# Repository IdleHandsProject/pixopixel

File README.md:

# The PIXO Pixel
PIXO Pixel is a 16 x 16 RGB LED display that runs off of an ESP32.

This project is open source! 

If you want to build this yourself, you can find the Bill of Materials [here](https://www.findchips.com/org/10-open-hardware/list/85998-pixo-pixel-esp-board-and-led-board) on FindChips.

## Flashing Firmware Instructions
1. You need to have the current version of the [Arduino IDE](https://arduino.cc) installed
2. Ensure that you have the [Arduino ESP32 Boards](https://github.com/espressif/arduino-esp32) installed
3. Various other libraries are required for the example firmware; they are listed below under "Libraries used in Example Firmware"
4. Connect your pixo pixel to your computer and start Arduino
5. Under the "Tools" menu, select "Board->Adafruit ESP32 Feather"; Leave Flash frequency and Upload speed the default
6. Under Port, select the device your pixo is communicating over
7. Compile and upload
8. When the Arduino console says "Connecting....", press and hold both the boot and reset buttons simultaniously for 1 second; then release both buttons
9. You should start to see output about flashing
10. When the flash is complete, press the reset button on the pixo to start your new firmware

[Here](https://youtu.be/dVT4Nei8qHg) is a video of Sean going into detail demonstrating some of the examples

## Libraries used in Example Firmware
Install these to your sketchbook's `libraries` folder, usually located in `YOUR HOME/Documents/Arduino`

* [Adafruit GFX](https://github.com/adafruit/Adafruit-GFX-Library)
* [Adafruit DotStar](https://github.com/adafruit/Adafruit_DotStar)
* [Adafruit DotStar Matrix](https://github.com/adafruit/Adafruit_DotStarMatrix)
* [ArduinoJson](https://github.com/bblanchon/ArduinoJson)
* [i2cdevlib](https://github.com/jrowberg/i2cdevlib)

**Note** Arduino IDE was complaining about i2cdevlib being invalid as the installation instructions are a bit unclear.
It seems that the ESP32 is not officially supported for use with these libraries, and I had to apply a patch ([#367](https://github.com/jrowberg/i2cdevlib/pull/367)) to get no compile errors.

### Patching I2Cdev and MPU6050 Libraries
1. Download i2cdevlib and extract the zip file
2. Inside the i2cdevlib/Arduino folder, copy `I2Cdev` and `MPU6050` folders to your `libraries` folder
3. Edit `libraries/I2Cdev/I2Cdev.cpp`, and immedietly under `#include "I2Cdev.h"`, add the following
```
#ifdef ARDUINO_ARCH_ESP32
#define BUFFER_LENGTH I2C_BUFFER_LENGTH
#endif
```
4. Edit `libraries/MPU6050/MPU6050_6Axis_MotionApps20.h` and add the following right above the `DEBUG` section
```
#ifndef ARDUINO_ARCH_ESP32
    typedef void prog_void;
    typedef char prog_char;
    typedef unsigned char prog_uchar;
    typedef int8_t prog_int8_t;
    typedef uint8_t prog_uint8_t;
    typedef int16_t prog_int16_t;
    typedef uint16_t prog_uint16_t;
    typedef int32_t prog_int32_t;
    typedef uint32_t prog_uint32_t;
#endif
```
5. Restart Arduino

There's a whole bunch of other commits in here, but this seems mostly to be a mix of: feature adding, bug fixing, and various other changes that may or may not be related. Feel free to experiment with these at your own discretion.

## Kickstarter - Success
This was a [Make100 Kickstarter](https://www.kickstarter.com/projects/idlehandsdev/pixo-pixel-an-esp32-based-iot-rgb-display-for-make) that was recently fulfilled

[Completion Video](https://youtu.be/YA3uAYVbMNc)

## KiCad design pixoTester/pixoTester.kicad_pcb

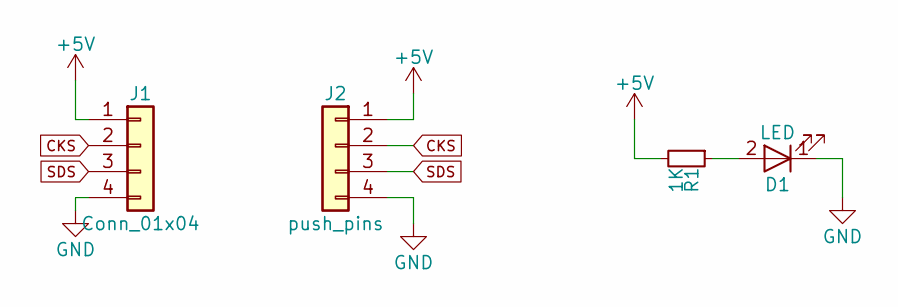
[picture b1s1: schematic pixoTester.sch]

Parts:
D1: LED; LED-0603
J1: Conn_01x04; Connectors_JST_S4B-PH-SM4-TB
J2: push_pins; pixo_testpins
R1: 1K; R_0805

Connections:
+5V: J1.1, J2.1, R1.2
CKS: J1.2, J2.2
GND: D1.1 (K), J1.4, J2.4
unnamed: D1.2 (A), R1.1
SDS: J1.3, J2.3

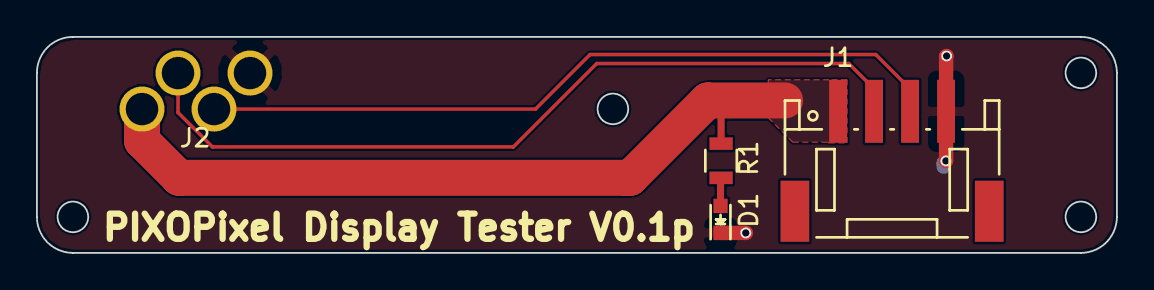
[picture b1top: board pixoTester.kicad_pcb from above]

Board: 2 copper layers, 60.0 x 12.0 mm, 4 parts (0 on the bottom side), 5 nets.

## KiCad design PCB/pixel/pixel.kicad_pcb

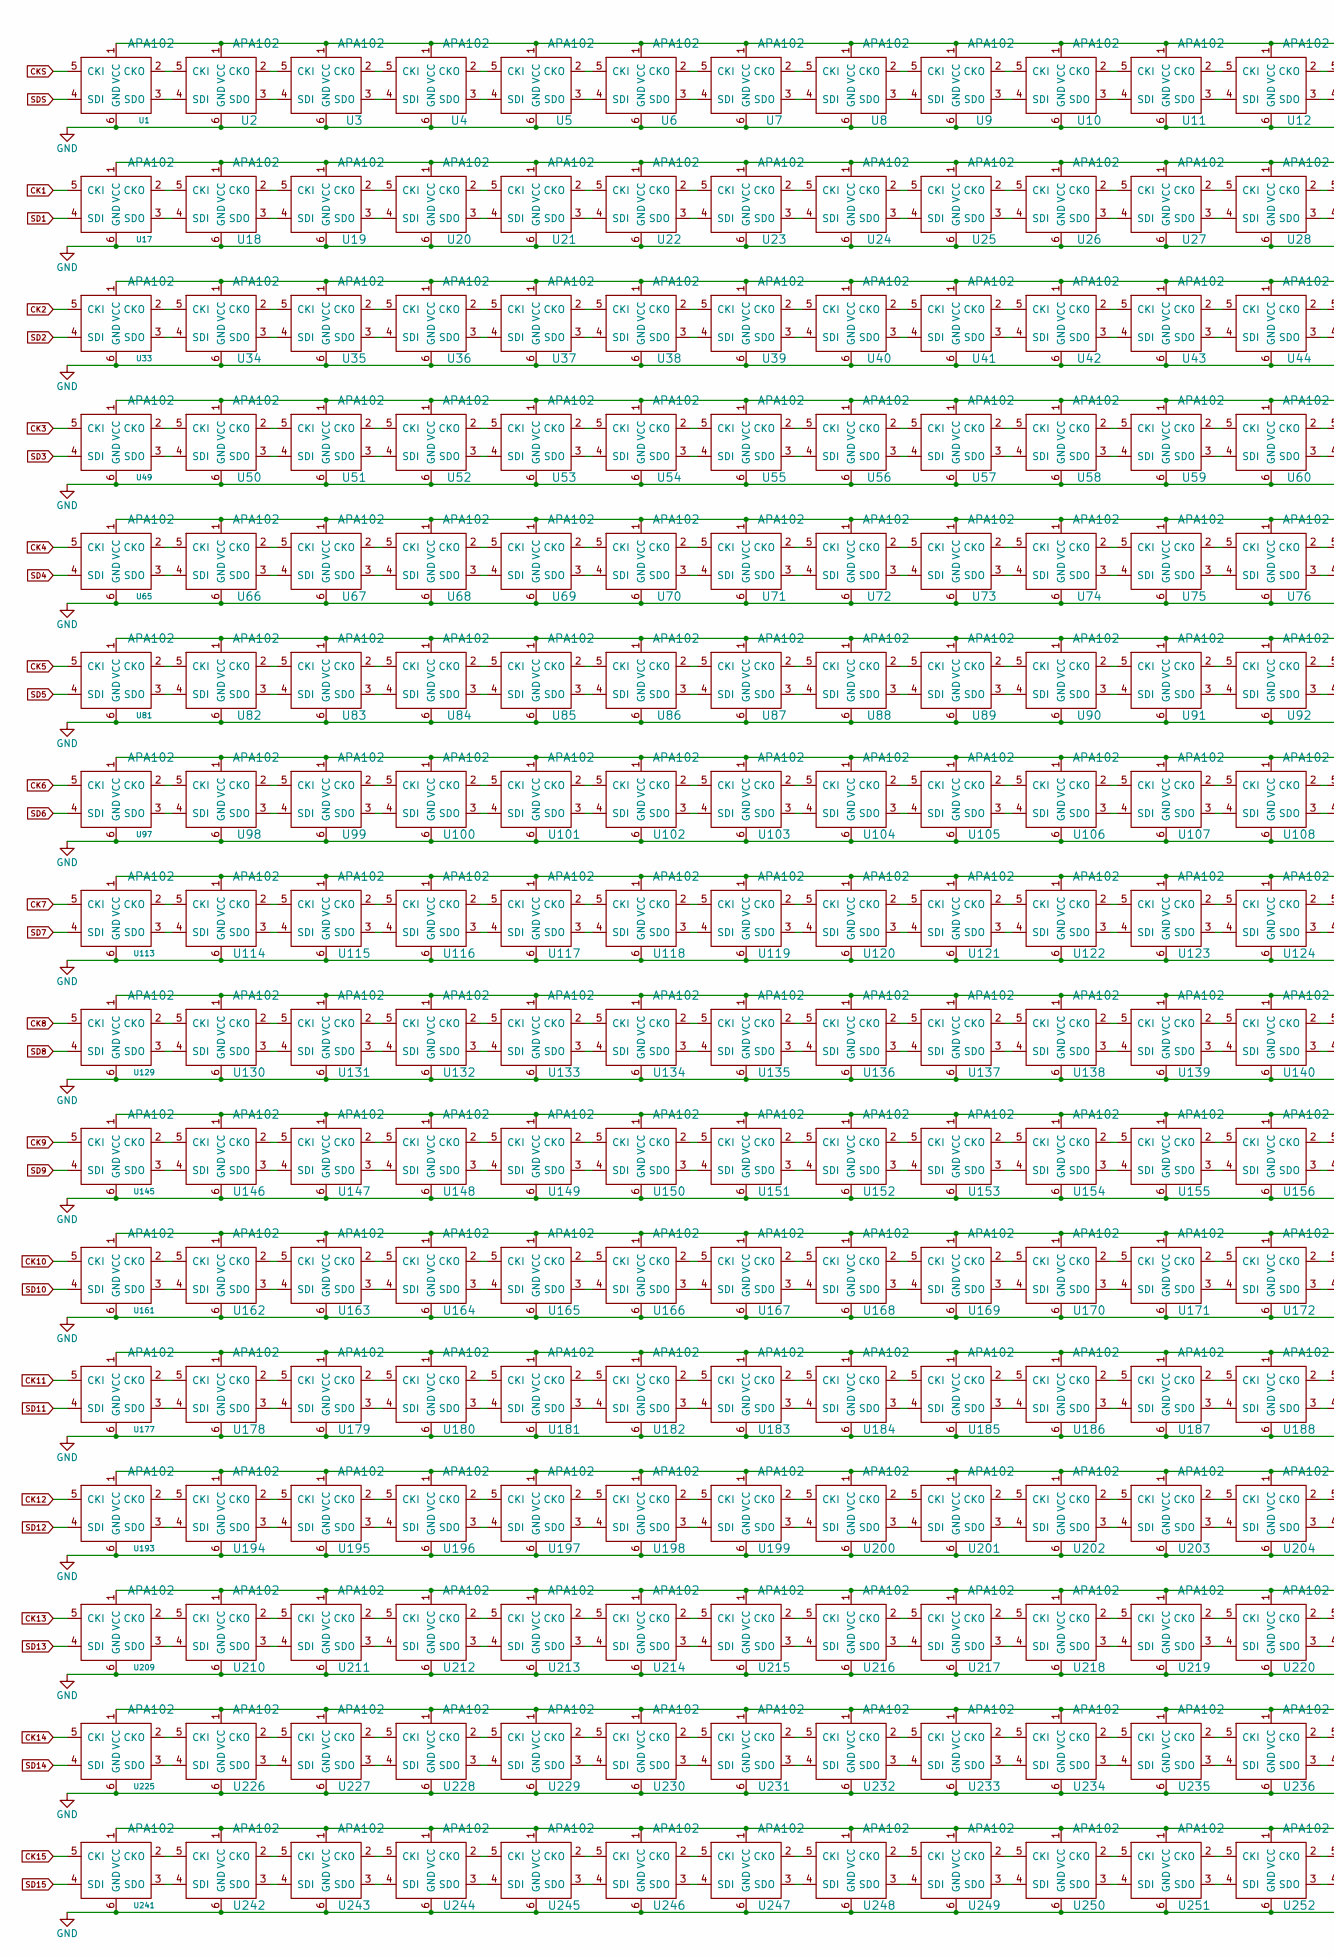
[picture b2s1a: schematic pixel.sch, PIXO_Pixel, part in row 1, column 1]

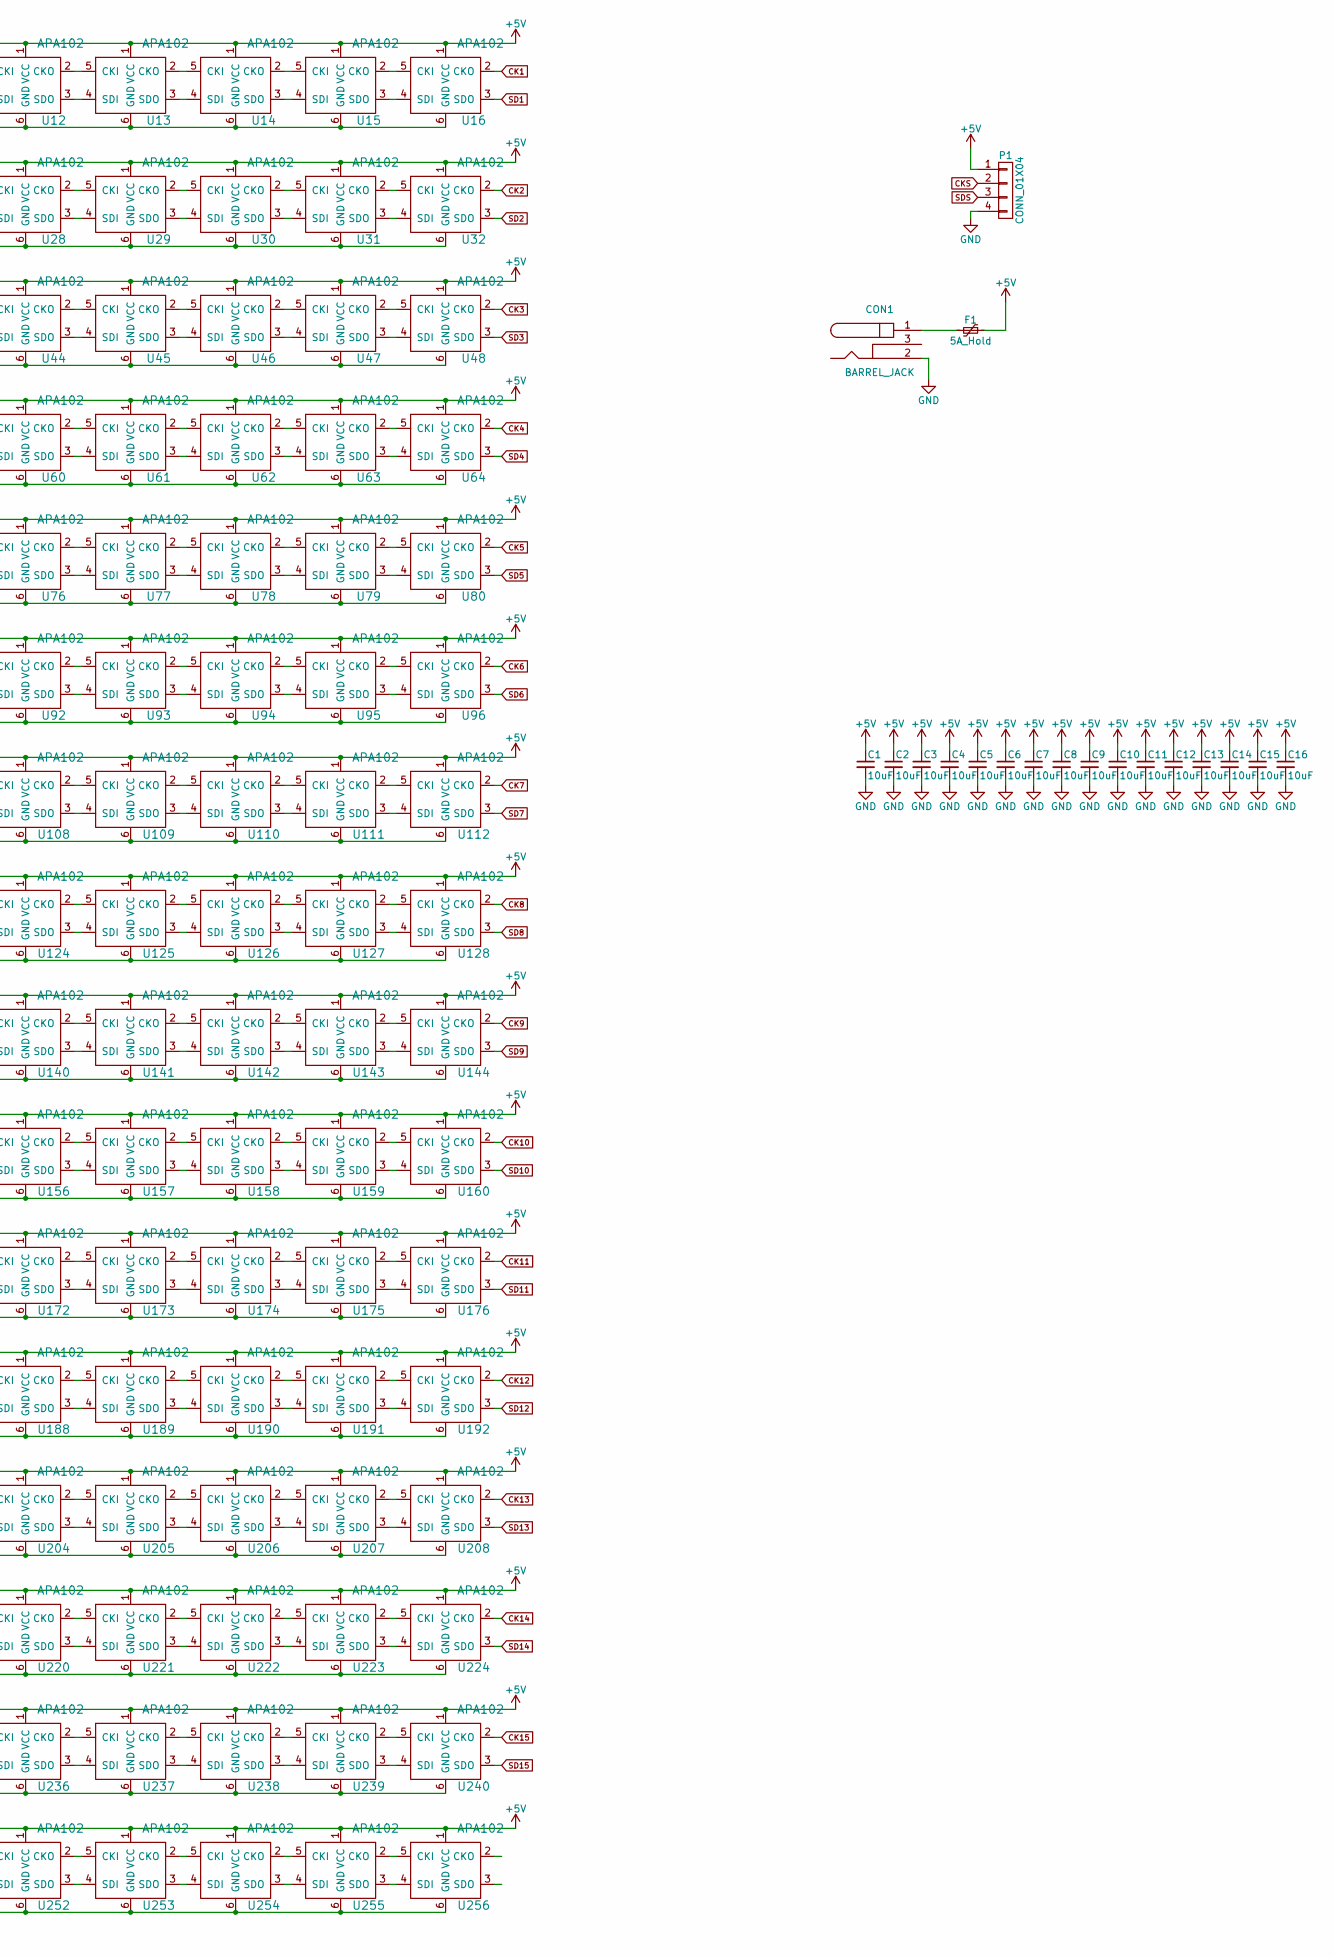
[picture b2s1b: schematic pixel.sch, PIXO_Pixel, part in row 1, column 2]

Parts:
C1: 10uF; c_1206; Digikey Part No. 490-3340-1-ND
C2, C3, C4, C5, C6, C7, C8, C9, C10, C11, C12, C13, C14, C15, C16: 10uF; c_1206; Digikey Part No. 490-5525-1-ND
CON1: BARREL_JACK; DC_POWERJACK_VERT_NoHoles; Digikey Part No. CP-006APJCT-ND
F1: 5A_Hold; Fuse_SMD1206_Reflow; Digikey Part No. MF-USML400-2CT-ND
P1: CONN_01X04; Connectors_JST_S4B-PH-SM4-TB; Digikey Part No. 455-1751-1-ND
U1, U2, U3, U4, U5, U6, U7, U8, U9, U10, U11, U12, U13, U14, U15, U16, U17, U18, U19, U20, U21, U22, U23, U24, U25, U26, U27, U28, U29, U30, U31, U32, U33, U34, U35, U36, U37, U38, U39, U40, U41, U42, U43, U44, U45, U46, U47, U48, U49, U50, U51, U52, U53, U54, U55, U56, U57, U58, U59, U60, U61, U62, U63, U64, U65, U66, U67, U68, U69, U70, U71, U72, U73, U74, U75, U76, U77, U78, U79, U80, U81, U82, U83, U84, U85, U86, U87, U88, U89, U90, U91, U92, U93, U94, U95, U96, U97, U98, U99, U100, U101, U102, U103, U104, U105, U106, U107, U108, U109, U110, U111, U112, U113, U114, U115, U116, U117, U118, U119, U120, U121, U122, U123, U124, U125, U126, U127, U128, U129, U130, U131, U132, U133, U134, U135, U136, U137, U138, U139, U140, U141, U142, U143, U144, U145, U146, U147, U148, U149, U150, U151, U152, U153, U154, U155, U156, U157, U158, U159, U160, U161, U162, U163, U164, U165, U166, U167, U168, U169, U170, U171, U172, U173, U174, U175, U176, U177, U178, U179, U180, U181, U182, U183, U184, U185, U186, U187, U188, U189, U190, U191, U192, U193, U194, U195, U196, U197, U198, U199, U200, U201, U202, U203, U204, U205, U206, U207, U208, U209, U210, U211, U212, U213, U214, U215, U216, U217, U218, U219, U220, U221, U222, U223, U224, U225, U226, U227, U228, U229, U230, U231, U232, U233, U234, U235, U236, U237, U238, U239, U240, U241, U242, U243, U244, U245, U246, U247, U248, U249, U250, U251, U252, U253, U254, U255, U256: APA102; APA102-2020_AFSTYLE

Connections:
+5V: C1.1, C2.1, C3.1, C4.1, C5.1, C6.1, C7.1, C8.1, C9.1, C10.1, C11.1, C12.1, C13.1, C14.1, C15.1, C16.1, F1.1, P1.1, U1.1 (VCC), U2.1 (VCC), U3.1 (VCC), U4.1 (VCC), U5.1 (VCC), U6.1 (VCC), U7.1 (VCC), U8.1 (VCC), U9.1 (VCC), U10.1 (VCC), U11.1 (VCC), U12.1 (VCC), U13.1 (VCC), U14.1 (VCC), U15.1 (VCC), U16.1 (VCC), U17.1 (VCC), U18.1 (VCC), U19.1 (VCC), U20.1 (VCC), U21.1 (VCC), U22.1 (VCC), U23.1 (VCC), U24.1 (VCC), U25.1 (VCC), U26.1 (VCC), U27.1 (VCC), U28.1 (VCC), U29.1 (VCC), U30.1 (VCC), U31.1 (VCC), U32.1 (VCC), U33.1 (VCC), U34.1 (VCC), U35.1 (VCC), U36.1 (VCC), U37.1 (VCC), U38.1 (VCC), U39.1 (VCC), U40.1 (VCC), U41.1 (VCC), U42.1 (VCC), U43.1 (VCC), U44.1 (VCC), U45.1 (VCC), U46.1 (VCC), U47.1 (VCC), U48.1 (VCC), U49.1 (VCC), U50.1 (VCC), U51.1 (VCC), U52.1 (VCC), U53.1 (VCC), U54.1 (VCC), U55.1 (VCC), U56.1 (VCC), U57.1 (VCC), U58.1 (VCC), U59.1 (VCC), U60.1 (VCC), U61.1 (VCC), U62.1 (VCC), U63.1 (VCC), U64.1 (VCC), U65.1 (VCC), U66.1 (VCC), U67.1 (VCC), U68.1 (VCC), U69.1 (VCC), U70.1 (VCC), U71.1 (VCC), U72.1 (VCC), U73.1 (VCC), U74.1 (VCC), U75.1 (VCC), U76.1 (VCC), U77.1 (VCC), U78.1 (VCC), U79.1 (VCC), U80.1 (VCC), U81.1 (VCC), U82.1 (VCC), U83.1 (VCC), U84.1 (VCC), U85.1 (VCC), U86.1 (VCC), U87.1 (VCC), U88.1 (VCC), U89.1 (VCC), U90.1 (VCC), U91.1 (VCC), U92.1 (VCC), U93.1 (VCC), U94.1 (VCC), U95.1 (VCC), U96.1 (VCC), U97.1 (VCC), U98.1 (VCC), U99.1 (VCC), U100.1 (VCC), U101.1 (VCC), U102.1 (VCC), U103.1 (VCC), U104.1 (VCC), U105.1 (VCC), U106.1 (VCC), U107.1 (VCC), U108.1 (VCC), U109.1 (VCC), U110.1 (VCC), U111.1 (VCC), U112.1 (VCC), U113.1 (VCC), U114.1 (VCC), U115.1 (VCC), U116.1 (VCC), U117.1 (VCC), U118.1 (VCC), U119.1 (VCC), U120.1 (VCC), U121.1 (VCC), U122.1 (VCC), U123.1 (VCC), U124.1 (VCC), U125.1 (VCC), U126.1 (VCC), U127.1 (VCC), U128.1 (VCC), U129.1 (VCC), U130.1 (VCC), U131.1 (VCC), U132.1 (VCC), U133.1 (VCC), U134.1 (VCC), U135.1 (VCC), U136.1 (VCC), U137.1 (VCC), U138.1 (VCC), U139.1 (VCC), U140.1 (VCC), U141.1 (VCC), U142.1 (VCC), U143.1 (VCC), U144.1 (VCC), U145.1 (VCC), U146.1 (VCC), U147.1 (VCC), U148.1 (VCC), U149.1 (VCC), U150.1 (VCC), U151.1 (VCC), U152.1 (VCC), U153.1 (VCC), U154.1 (VCC), U155.1 (VCC), U156.1 (VCC), U157.1 (VCC), U158.1 (VCC), U159.1 (VCC), U160.1 (VCC), U161.1 (VCC), U162.1 (VCC), U163.1 (VCC), U164.1 (VCC), U165.1 (VCC), U166.1 (VCC), U167.1 (VCC), U168.1 (VCC), U169.1 (VCC), U170.1 (VCC), U171.1 (VCC), U172.1 (VCC), U173.1 (VCC), U174.1 (VCC), U175.1 (VCC), U176.1 (VCC), U177.1 (VCC), U178.1 (VCC), U179.1 (VCC), U180.1 (VCC), U181.1 (VCC), U182.1 (VCC), U183.1 (VCC), U184.1 (VCC), U185.1 (VCC), U186.1 (VCC), U187.1 (VCC), U188.1 (VCC), U189.1 (VCC), U190.1 (VCC), U191.1 (VCC), U192.1 (VCC), U193.1 (VCC), U194.1 (VCC), U195.1 (VCC), U196.1 (VCC), U197.1 (VCC), U198.1 (VCC), U199.1 (VCC), U200.1 (VCC), U201.1 (VCC), U202.1 (VCC), U203.1 (VCC), U204.1 (VCC), U205.1 (VCC), U206.1 (VCC), U207.1 (VCC), U208.1 (VCC), U209.1 (VCC), U210.1 (VCC), U211.1 (VCC), U212.1 (VCC), U213.1 (VCC), U214.1 (VCC), U215.1 (VCC), U216.1 (VCC), U217.1 (VCC), U218.1 (VCC), U219.1 (VCC), U220.1 (VCC), U221.1 (VCC), U222.1 (VCC), U223.1 (VCC), U224.1 (VCC), U225.1 (VCC), U226.1 (VCC), U227.1 (VCC), U228.1 (VCC), U229.1 (VCC), U230.1 (VCC), U231.1 (VCC), U232.1 (VCC), U233.1 (VCC), U234.1 (VCC), U235.1 (VCC), U236.1 (VCC), U237.1 (VCC), U238.1 (VCC), U239.1 (VCC), U240.1 (VCC), U241.1 (VCC), U242.1 (VCC), U243.1 (VCC), U244.1 (VCC), U245.1 (VCC), U246.1 (VCC), U247.1 (VCC), U248.1 (VCC), U249.1 (VCC), U250.1 (VCC), U251.1 (VCC), U252.1 (VCC), U253.1 (VCC), U254.1 (VCC), U255.1 (VCC), U256.1 (VCC)
CK1: U16.2 (CKO), U17.5 (CKI)
CK2: U32.2 (CKO), U33.5 (CKI)
CK3: U48.2 (CKO), U49.5 (CKI)
CK4: U64.2 (CKO), U65.5 (CKI)
CK5: U80.2 (CKO), U81.5 (CKI)
CK6: U96.2 (CKO), U97.5 (CKI)
CK7: U112.2 (CKO), U113.5 (CKI)
CK8: U128.2 (CKO), U129.5 (CKI)
CK9: U144.2 (CKO), U145.5 (CKI)
CK10: U160.2 (CKO), U161.5 (CKI)
CK11: U176.2 (CKO), U177.5 (CKI)
CK12: U192.2 (CKO), U193.5 (CKI)
CK13: U208.2 (CKO), U209.5 (CKI)
CK14: U224.2 (CKO), U225.5 (CKI)
CK15: U240.2 (CKO), U241.5 (CKI)
CKS: P1.2, U1.5 (CKI)
GND: C1.2, C2.2, C3.2, C4.2, C5.2, C6.2, C7.2, C8.2, C9.2, C10.2, C11.2, C12.2, C13.2, C14.2, C15.2, C16.2, CON1.2, P1.4, U1.6 (GND), U2.6 (GND), U3.6 (GND), U4.6 (GND), U5.6 (GND), U6.6 (GND), U7.6 (GND), U8.6 (GND), U9.6 (GND), U10.6 (GND), U11.6 (GND), U12.6 (GND), U13.6 (GND), U14.6 (GND), U15.6 (GND), U16.6 (GND), U17.6 (GND), U18.6 (GND), U19.6 (GND), U20.6 (GND), U21.6 (GND), U22.6 (GND), U23.6 (GND), U24.6 (GND), U25.6 (GND), U26.6 (GND), U27.6 (GND), U28.6 (GND), U29.6 (GND), U30.6 (GND), U31.6 (GND), U32.6 (GND), U33.6 (GND), U34.6 (GND), U35.6 (GND), U36.6 (GND), U37.6 (GND), U38.6 (GND), U39.6 (GND), U40.6 (GND), U41.6 (GND), U42.6 (GND), U43.6 (GND), U44.6 (GND), U45.6 (GND), U46.6 (GND), U47.6 (GND), U48.6 (GND), U49.6 (GND), U50.6 (GND), U51.6 (GND), U52.6 (GND), U53.6 (GND), U54.6 (GND), U55.6 (GND), U56.6 (GND), U57.6 (GND), U58.6 (GND), U59.6 (GND), U60.6 (GND), U61.6 (GND), U62.6 (GND), U63.6 (GND), U64.6 (GND), U65.6 (GND), U66.6 (GND), U67.6 (GND), U68.6 (GND), U69.6 (GND), U70.6 (GND), U71.6 (GND), U72.6 (GND), U73.6 (GND), U74.6 (GND), U75.6 (GND), U76.6 (GND), U77.6 (GND), U78.6 (GND), U79.6 (GND), U80.6 (GND), U81.6 (GND), U82.6 (GND), U83.6 (GND), U84.6 (GND), U85.6 (GND), U86.6 (GND), U87.6 (GND), U88.6 (GND), U89.6 (GND), U90.6 (GND), U91.6 (GND), U92.6 (GND), U93.6 (GND), U94.6 (GND), U95.6 (GND), U96.6 (GND), U97.6 (GND), U98.6 (GND), U99.6 (GND), U100.6 (GND), U101.6 (GND), U102.6 (GND), U103.6 (GND), U104.6 (GND), U105.6 (GND), U106.6 (GND), U107.6 (GND), U108.6 (GND), U109.6 (GND), U110.6 (GND), U111.6 (GND), U112.6 (GND), U113.6 (GND), U114.6 (GND), U115.6 (GND), U116.6 (GND), U117.6 (GND), U118.6 (GND), U119.6 (GND), U120.6 (GND), U121.6 (GND), U122.6 (GND), U123.6 (GND), U124.6 (GND), U125.6 (GND), U126.6 (GND), U127.6 (GND), U128.6 (GND), U129.6 (GND), U130.6 (GND), U131.6 (GND), U132.6 (GND), U133.6 (GND), U134.6 (GND), U135.6 (GND), U136.6 (GND), U137.6 (GND), U138.6 (GND), U139.6 (GND), U140.6 (GND), U141.6 (GND), U142.6 (GND), U143.6 (GND), U144.6 (GND), U145.6 (GND), U146.6 (GND), U147.6 (GND), U148.6 (GND), U149.6 (GND), U150.6 (GND), U151.6 (GND), U152.6 (GND), U153.6 (GND), U154.6 (GND), U155.6 (GND), U156.6 (GND), U157.6 (GND), U158.6 (GND), U159.6 (GND), U160.6 (GND), U161.6 (GND), U162.6 (GND), U163.6 (GND), U164.6 (GND), U165.6 (GND), U166.6 (GND), U167.6 (GND), U168.6 (GND), U169.6 (GND), U170.6 (GND), U171.6 (GND), U172.6 (GND), U173.6 (GND), U174.6 (GND), U175.6 (GND), U176.6 (GND), U177.6 (GND), U178.6 (GND), U179.6 (GND), U180.6 (GND), U181.6 (GND), U182.6 (GND), U183.6 (GND), U184.6 (GND), U185.6 (GND), U186.6 (GND), U187.6 (GND), U188.6 (GND), U189.6 (GND), U190.6 (GND), U191.6 (GND), U192.6 (GND), U193.6 (GND), U194.6 (GND), U195.6 (GND), U196.6 (GND), U197.6 (GND), U198.6 (GND), U199.6 (GND), U200.6 (GND), U201.6 (GND), U202.6 (GND), U203.6 (GND), U204.6 (GND), U205.6 (GND), U206.6 (GND), U207.6 (GND), U208.6 (GND), U209.6 (GND), U210.6 (GND), U211.6 (GND), U212.6 (GND), U213.6 (GND), U214.6 (GND), U215.6 (GND), U216.6 (GND), U217.6 (GND), U218.6 (GND), U219.6 (GND), U220.6 (GND), U221.6 (GND), U222.6 (GND), U223.6 (GND), U224.6 (GND), U225.6 (GND), U226.6 (GND), U227.6 (GND), U228.6 (GND), U229.6 (GND), U230.6 (GND), U231.6 (GND), U232.6 (GND), U233.6 (GND), U234.6 (GND), U235.6 (GND), U236.6 (GND), U237.6 (GND), U238.6 (GND), U239.6 (GND), U240.6 (GND), U241.6 (GND), U242.6 (GND), U243.6 (GND), U244.6 (GND), U245.6 (GND), U246.6 (GND), U247.6 (GND), U248.6 (GND), U249.6 (GND), U250.6 (GND), U251.6 (GND), U252.6 (GND), U253.6 (GND), U254.6 (GND), U255.6 (GND), U256.6 (GND)
unnamed: CON1.1, F1.2
unnamed: U1.2 (CKO), U2.5 (CKI)
unnamed: U1.3 (SDO), U2.4 (SDI)
unnamed: U2.2 (CKO), U3.5 (CKI)
unnamed: U2.3 (SDO), U3.4 (SDI)
unnamed: U3.2 (CKO), U4.5 (CKI)
unnamed: U3.3 (SDO), U4.4 (SDI)
unnamed: U4.2 (CKO), U5.5 (CKI)
unnamed: U4.3 (SDO), U5.4 (SDI)
unnamed: U5.2 (CKO), U6.5 (CKI)
unnamed: U5.3 (SDO), U6.4 (SDI)
unnamed: U6.2 (CKO), U7.5 (CKI)
unnamed: U6.3 (SDO), U7.4 (SDI)
unnamed: U7.2 (CKO), U8.5 (CKI)
unnamed: U7.3 (SDO), U8.4 (SDI)
unnamed: U8.2 (CKO), U9.5 (CKI)
unnamed: U8.3 (SDO), U9.4 (SDI)
unnamed: U10.2 (CKO), U11.5 (CKI)
unnamed: U10.3 (SDO), U11.4 (SDI)
unnamed: U9.3 (SDO), U10.4 (SDI)
unnamed: U9.2 (CKO), U10.5 (CKI)
unnamed: U11.2 (CKO), U12.5 (CKI)
unnamed: U11.3 (SDO), U12.4 (SDI)
unnamed: U12.2 (CKO), U13.5 (CKI)
unnamed: U12.3 (SDO), U13.4 (SDI)
unnamed: U13.2 (CKO), U14.5 (CKI)
unnamed: U13.3 (SDO), U14.4 (SDI)
unnamed: U14.2 (CKO), U15.5 (CKI)
unnamed: U14.3 (SDO), U15.4 (SDI)
unnamed: U15.2 (CKO), U16.5 (CKI)
unnamed: U15.3 (SDO), U16.4 (SDI)
unnamed: U17.2 (CKO), U18.5 (CKI)
unnamed: U17.3 (SDO), U18.4 (SDI)
unnamed: U18.2 (CKO), U19.5 (CKI)
unnamed: U18.3 (SDO), U19.4 (SDI)
unnamed: U19.2 (CKO), U20.5 (CKI)
unnamed: U19.3 (SDO), U20.4 (SDI)
unnamed: U20.2 (CKO), U21.5 (CKI)
unnamed: U20.3 (SDO), U21.4 (SDI)
unnamed: U21.2 (CKO), U22.5 (CKI)
unnamed: U21.3 (SDO), U22.4 (SDI)
unnamed: U22.2 (CKO), U23.5 (CKI)
unnamed: U22.3 (SDO), U23.4 (SDI)
unnamed: U23.2 (CKO), U24.5 (CKI)
unnamed: U23.3 (SDO), U24.4 (SDI)
unnamed: U24.2 (CKO), U25.5 (CKI)
unnamed: U24.3 (SDO), U25.4 (SDI)
unnamed: U25.2 (CKO), U26.5 (CKI)
unnamed: U25.3 (SDO), U26.4 (SDI)
unnamed: U26.2 (CKO), U27.5 (CKI)
unnamed: U26.3 (SDO), U27.4 (SDI)
unnamed: U27.2 (CKO), U28.5 (CKI)
unnamed: U27.3 (SDO), U28.4 (SDI)
unnamed: U28.2 (CKO), U29.5 (CKI)
unnamed: U28.3 (SDO), U29.4 (SDI)
unnamed: U29.2 (CKO), U30.5 (CKI)
unnamed: U29.3 (SDO), U30.4 (SDI)
unnamed: U30.2 (CKO), U31.5 (CKI)
unnamed: U30.3 (SDO), U31.4 (SDI)
unnamed: U31.2 (CKO), U32.5 (CKI)
unnamed: U31.3 (SDO), U32.4 (SDI)
unnamed: U33.2 (CKO), U34.5 (CKI)
unnamed: U33.3 (SDO), U34.4 (SDI)
unnamed: U34.2 (CKO), U35.5 (CKI)
unnamed: U34.3 (SDO), U35.4 (SDI)
unnamed: U35.2 (CKO), U36.5 (CKI)
unnamed: U35.3 (SDO), U36.4 (SDI)
unnamed: U36.2 (CKO), U37.5 (CKI)
unnamed: U36.3 (SDO), U37.4 (SDI)
unnamed: U37.2 (CKO), U38.5 (CKI)
unnamed: U37.3 (SDO), U38.4 (SDI)
unnamed: U38.2 (CKO), U39.5 (CKI)
unnamed: U38.3 (SDO), U39.4 (SDI)
unnamed: U39.2 (CKO), U40.5 (CKI)
unnamed: U39.3 (SDO), U40.4 (SDI)
unnamed: U40.2 (CKO), U41.5 (CKI)
unnamed: U40.3 (SDO), U41.4 (SDI)
unnamed: U41.2 (CKO), U42.5 (CKI)
unnamed: U41.3 (SDO), U42.4 (SDI)
unnamed: U42.2 (CKO), U43.5 (CKI)
unnamed: U42.3 (SDO), U43.4 (SDI)
unnamed: U43.2 (CKO), U44.5 (CKI)
unnamed: U43.3 (SDO), U44.4 (SDI)
unnamed: U44.2 (CKO), U45.5 (CKI)
unnamed: U44.3 (SDO), U45.4 (SDI)
unnamed: U45.2 (CKO), U46.5 (CKI)
unnamed: U45.3 (SDO), U46.4 (SDI)
unnamed: U46.2 (CKO), U47.5 (CKI)
unnamed: U46.3 (SDO), U47.4 (SDI)
unnamed: U47.2 (CKO), U48.5 (CKI)
unnamed: U47.3 (SDO), U48.4 (SDI)
unnamed: U49.2 (CKO), U50.5 (CKI)
unnamed: U49.3 (SDO), U50.4 (SDI)
unnamed: U50.2 (CKO), U51.5 (CKI)
unnamed: U50.3 (SDO), U51.4 (SDI)
unnamed: U51.2 (CKO), U52.5 (CKI)
unnamed: U51.3 (SDO), U52.4 (SDI)
unnamed: U52.2 (CKO), U53.5 (CKI)
unnamed: U52.3 (SDO), U53.4 (SDI)
unnamed: U53.2 (CKO), U54.5 (CKI)
unnamed: U53.3 (SDO), U54.4 (SDI)
unnamed: U54.2 (CKO), U55.5 (CKI)
unnamed: U54.3 (SDO), U55.4 (SDI)
unnamed: U55.2 (CKO), U56.5 (CKI)
unnamed: U55.3 (SDO), U56.4 (SDI)
unnamed: U56.2 (CKO), U57.5 (CKI)
unnamed: U56.3 (SDO), U57.4 (SDI)
unnamed: U57.2 (CKO), U58.5 (CKI)
unnamed: U57.3 (SDO), U58.4 (SDI)
unnamed: U58.2 (CKO), U59.5 (CKI)
unnamed: U58.3 (SDO), U59.4 (SDI)
unnamed: U59.2 (CKO), U60.5 (CKI)
unnamed: U59.3 (SDO), U60.4 (SDI)
unnamed: U60.2 (CKO), U61.5 (CKI)
unnamed: U60.3 (SDO), U61.4 (SDI)
unnamed: U61.2 (CKO), U62.5 (CKI)
unnamed: U61.3 (SDO), U62.4 (SDI)
unnamed: U62.2 (CKO), U63.5 (CKI)
unnamed: U62.3 (SDO), U63.4 (SDI)
unnamed: U63.2 (CKO), U64.5 (CKI)
unnamed: U63.3 (SDO), U64.4 (SDI)
unnamed: U65.2 (CKO), U66.5 (CKI)
unnamed: U65.3 (SDO), U66.4 (SDI)
unnamed: U66.2 (CKO), U67.5 (CKI)
unnamed: U66.3 (SDO), U67.4 (SDI)
unnamed: U67.2 (CKO), U68.5 (CKI)
unnamed: U67.3 (SDO), U68.4 (SDI)
unnamed: U68.2 (CKO), U69.5 (CKI)
unnamed: U68.3 (SDO), U69.4 (SDI)
unnamed: U69.2 (CKO), U70.5 (CKI)
unnamed: U69.3 (SDO), U70.4 (SDI)
unnamed: U70.2 (CKO), U71.5 (CKI)
unnamed: U70.3 (SDO), U71.4 (SDI)
unnamed: U71.2 (CKO), U72.5 (CKI)
unnamed: U71.3 (SDO), U72.4 (SDI)
unnamed: U72.2 (CKO), U73.5 (CKI)
unnamed: U72.3 (SDO), U73.4 (SDI)
unnamed: U73.2 (CKO), U74.5 (CKI)
unnamed: U73.3 (SDO), U74.4 (SDI)
unnamed: U74.2 (CKO), U75.5 (CKI)
unnamed: U74.3 (SDO), U75.4 (SDI)
unnamed: U75.2 (CKO), U76.5 (CKI)
unnamed: U75.3 (SDO), U76.4 (SDI)
unnamed: U76.2 (CKO), U77.5 (CKI)
unnamed: U76.3 (SDO), U77.4 (SDI)
unnamed: U77.2 (CKO), U78.5 (CKI)
unnamed: U77.3 (SDO), U78.4 (SDI)
unnamed: U78.2 (CKO), U79.5 (CKI)
unnamed: U78.3 (SDO), U79.4 (SDI)
unnamed: U79.2 (CKO), U80.5 (CKI)
unnamed: U79.3 (SDO), U80.4 (SDI)
unnamed: U81.2 (CKO), U82.5 (CKI)
unnamed: U81.3 (SDO), U82.4 (SDI)
unnamed: U82.2 (CKO), U83.5 (CKI)
unnamed: U82.3 (SDO), U83.4 (SDI)
unnamed: U83.2 (CKO), U84.5 (CKI)
unnamed: U83.3 (SDO), U84.4 (SDI)
unnamed: U84.2 (CKO), U85.5 (CKI)
unnamed: U84.3 (SDO), U85.4 (SDI)
unnamed: U85.2 (CKO), U86.5 (CKI)
unnamed: U85.3 (SDO), U86.4 (SDI)
unnamed: U86.2 (CKO), U87.5 (CKI)
unnamed: U86.3 (SDO), U87.4 (SDI)
unnamed: U87.2 (CKO), U88.5 (CKI)
unnamed: U87.3 (SDO), U88.4 (SDI)
unnamed: U88.2 (CKO), U89.5 (CKI)
unnamed: U88.3 (SDO), U89.4 (SDI)
unnamed: U89.2 (CKO), U90.5 (CKI)
unnamed: U89.3 (SDO), U90.4 (SDI)
unnamed: U90.2 (CKO), U91.5 (CKI)
unnamed: U90.3 (SDO), U91.4 (SDI)
unnamed: U91.2 (CKO), U92.5 (CKI)
unnamed: U91.3 (SDO), U92.4 (SDI)
unnamed: U92.2 (CKO), U93.5 (CKI)
unnamed: U92.3 (SDO), U93.4 (SDI)
unnamed: U93.2 (CKO), U94.5 (CKI)
unnamed: U93.3 (SDO), U94.4 (SDI)
unnamed: U94.2 (CKO), U95.5 (CKI)
unnamed: U94.3 (SDO), U95.4 (SDI)
unnamed: U95.2 (CKO), U96.5 (CKI)
unnamed: U95.3 (SDO), U96.4 (SDI)
unnamed: U97.2 (CKO), U98.5 (CKI)
unnamed: U97.3 (SDO), U98.4 (SDI)
unnamed: U98.2 (CKO), U99.5 (CKI)
unnamed: U98.3 (SDO), U99.4 (SDI)
unnamed: U100.2 (CKO), U101.5 (CKI)
unnamed: U100.3 (SDO), U101.4 (SDI)
unnamed: U99.3 (SDO), U100.4 (SDI)
unnamed: U99.2 (CKO), U100.5 (CKI)
unnamed: U101.2 (CKO), U102.5 (CKI)
unnamed: U101.3 (SDO), U102.4 (SDI)
unnamed: U102.2 (CKO), U103.5 (CKI)
unnamed: U102.3 (SDO), U103.4 (SDI)
unnamed: U103.2 (CKO), U104.5 (CKI)
unnamed: U103.3 (SDO), U104.4 (SDI)
unnamed: U104.2 (CKO), U105.5 (CKI)
unnamed: U104.3 (SDO), U105.4 (SDI)
unnamed: U105.2 (CKO), U106.5 (CKI)
unnamed: U105.3 (SDO), U106.4 (SDI)
unnamed: U106.2 (CKO), U107.5 (CKI)
unnamed: U106.3 (SDO), U107.4 (SDI)
unnamed: U107.2 (CKO), U108.5 (CKI)
unnamed: U107.3 (SDO), U108.4 (SDI)
unnamed: U108.2 (CKO), U109.5 (CKI)
unnamed: U108.3 (SDO), U109.4 (SDI)
unnamed: U109.2 (CKO), U110.5 (CKI)
unnamed: U109.3 (SDO), U110.4 (SDI)
unnamed: U110.2 (CKO), U111.5 (CKI)
unnamed: U110.3 (SDO), U111.4 (SDI)
unnamed: U111.2 (CKO), U112.5 (CKI)
unnamed: U111.3 (SDO), U112.4 (SDI)
unnamed: U113.2 (CKO), U114.5 (CKI)
unnamed: U113.3 (SDO), U114.4 (SDI)
unnamed: U114.2 (CKO), U115.5 (CKI)
unnamed: U114.3 (SDO), U115.4 (SDI)
unnamed: U115.2 (CKO), U116.5 (CKI)
unnamed: U115.3 (SDO), U116.4 (SDI)
unnamed: U116.2 (CKO), U117.5 (CKI)
unnamed: U116.3 (SDO), U117.4 (SDI)
unnamed: U117.2 (CKO), U118.5 (CKI)
unnamed: U117.3 (SDO), U118.4 (SDI)
unnamed: U118.2 (CKO), U119.5 (CKI)
unnamed: U118.3 (SDO), U119.4 (SDI)
unnamed: U119.2 (CKO), U120.5 (CKI)
unnamed: U119.3 (SDO), U120.4 (SDI)
unnamed: U120.2 (CKO), U121.5 (CKI)
unnamed: U120.3 (SDO), U121.4 (SDI)
unnamed: U121.2 (CKO), U122.5 (CKI)
unnamed: U121.3 (SDO), U122.4 (SDI)
unnamed: U122.2 (CKO), U123.5 (CKI)
unnamed: U122.3 (SDO), U123.4 (SDI)
unnamed: U123.2 (CKO), U124.5 (CKI)
unnamed: U123.3 (SDO), U124.4 (SDI)
unnamed: U124.2 (CKO), U125.5 (CKI)
unnamed: U124.3 (SDO), U125.4 (SDI)
unnamed: U125.2 (CKO), U126.5 (CKI)
unnamed: U125.3 (SDO), U126.4 (SDI)
unnamed: U126.2 (CKO), U127.5 (CKI)
unnamed: U126.3 (SDO), U127.4 (SDI)
unnamed: U127.2 (CKO), U128.5 (CKI)
unnamed: U127.3 (SDO), U128.4 (SDI)
unnamed: U129.2 (CKO), U130.5 (CKI)
unnamed: U129.3 (SDO), U130.4 (SDI)
unnamed: U130.2 (CKO), U131.5 (CKI)
unnamed: U130.3 (SDO), U131.4 (SDI)
unnamed: U131.2 (CKO), U132.5 (CKI)
unnamed: U131.3 (SDO), U132.4 (SDI)
unnamed: U132.2 (CKO), U133.5 (CKI)
unnamed: U132.3 (SDO), U133.4 (SDI)
unnamed: U133.2 (CKO), U134.5 (CKI)
unnamed: U133.3 (SDO), U134.4 (SDI)
unnamed: U134.2 (CKO), U135.5 (CKI)
unnamed: U134.3 (SDO), U135.4 (SDI)
unnamed: U135.2 (CKO), U136.5 (CKI)
unnamed: U135.3 (SDO), U136.4 (SDI)
unnamed: U136.2 (CKO), U137.5 (CKI)
unnamed: U136.3 (SDO), U137.4 (SDI)
unnamed: U137.2 (CKO), U138.5 (CKI)
unnamed: U137.3 (SDO), U138.4 (SDI)
unnamed: U138.2 (CKO), U139.5 (CKI)
unnamed: U138.3 (SDO), U139.4 (SDI)
unnamed: U139.2 (CKO), U140.5 (CKI)
unnamed: U139.3 (SDO), U140.4 (SDI)
unnamed: U140.2 (CKO), U141.5 (CKI)
unnamed: U140.3 (SDO), U141.4 (SDI)
unnamed: U141.2 (CKO), U142.5 (CKI)
unnamed: U141.3 (SDO), U142.4 (SDI)
unnamed: U142.2 (CKO), U143.5 (CKI)
unnamed: U142.3 (SDO), U143.4 (SDI)
unnamed: U143.2 (CKO), U144.5 (CKI)
unnamed: U143.3 (SDO), U144.4 (SDI)
unnamed: U145.2 (CKO), U146.5 (CKI)
unnamed: U145.3 (SDO), U146.4 (SDI)
unnamed: U146.2 (CKO), U147.5 (CKI)
unnamed: U146.3 (SDO), U147.4 (SDI)
unnamed: U147.2 (CKO), U148.5 (CKI)
unnamed: U147.3 (SDO), U148.4 (SDI)
unnamed: U148.2 (CKO), U149.5 (CKI)
unnamed: U148.3 (SDO), U149.4 (SDI)
unnamed: U149.2 (CKO), U150.5 (CKI)
unnamed: U149.3 (SDO), U150.4 (SDI)
unnamed: U150.2 (CKO), U151.5 (CKI)
unnamed: U150.3 (SDO), U151.4 (SDI)
unnamed: U151.2 (CKO), U152.5 (CKI)
unnamed: U151.3 (SDO), U152.4 (SDI)
unnamed: U152.2 (CKO), U153.5 (CKI)
unnamed: U152.3 (SDO), U153.4 (SDI)
unnamed: U153.2 (CKO), U154.5 (CKI)
unnamed: U153.3 (SDO), U154.4 (SDI)
unnamed: U154.2 (CKO), U155.5 (CKI)
unnamed: U154.3 (SDO), U155.4 (SDI)
unnamed: U155.2 (CKO), U156.5 (CKI)
unnamed: U155.3 (SDO), U156.4 (SDI)
unnamed: U156.2 (CKO), U157.5 (CKI)
unnamed: U156.3 (SDO), U157.4 (SDI)
unnamed: U157.2 (CKO), U158.5 (CKI)
unnamed: U157.3 (SDO), U158.4 (SDI)
unnamed: U158.2 (CKO), U159.5 (CKI)
unnamed: U158.3 (SDO), U159.4 (SDI)
unnamed: U159.2 (CKO), U160.5 (CKI)
unnamed: U159.3 (SDO), U160.4 (SDI)
unnamed: U161.2 (CKO), U162.5 (CKI)
unnamed: U161.3 (SDO), U162.4 (SDI)
unnamed: U162.2 (CKO), U163.5 (CKI)
unnamed: U162.3 (SDO), U163.4 (SDI)
unnamed: U163.2 (CKO), U164.5 (CKI)
unnamed: U163.3 (SDO), U164.4 (SDI)
unnamed: U164.2 (CKO), U165.5 (CKI)
unnamed: U164.3 (SDO), U165.4 (SDI)
unnamed: U165.2 (CKO), U166.5 (CKI)
unnamed: U165.3 (SDO), U166.4 (SDI)
unnamed: U166.2 (CKO), U167.5 (CKI)
unnamed: U166.3 (SDO), U167.4 (SDI)
unnamed: U167.2 (CKO), U168.5 (CKI)
unnamed: U167.3 (SDO), U168.4 (SDI)
unnamed: U168.2 (CKO), U169.5 (CKI)
unnamed: U168.3 (SDO), U169.4 (SDI)
unnamed: U169.2 (CKO), U170.5 (CKI)
unnamed: U169.3 (SDO), U170.4 (SDI)
unnamed: U170.2 (CKO), U171.5 (CKI)
unnamed: U170.3 (SDO), U171.4 (SDI)
unnamed: U171.2 (CKO), U172.5 (CKI)
unnamed: U171.3 (SDO), U172.4 (SDI)
unnamed: U172.2 (CKO), U173.5 (CKI)
unnamed: U172.3 (SDO), U173.4 (SDI)
unnamed: U173.2 (CKO), U174.5 (CKI)
unnamed: U173.3 (SDO), U174.4 (SDI)
unnamed: U174.2 (CKO), U175.5 (CKI)
unnamed: U174.3 (SDO), U175.4 (SDI)
unnamed: U175.2 (CKO), U176.5 (CKI)
unnamed: U175.3 (SDO), U176.4 (SDI)
unnamed: U177.2 (CKO), U178.5 (CKI)
unnamed: U177.3 (SDO), U178.4 (SDI)
unnamed: U178.2 (CKO), U179.5 (CKI)
unnamed: U178.3 (SDO), U179.4 (SDI)
unnamed: U179.2 (CKO), U180.5 (CKI)
unnamed: U179.3 (SDO), U180.4 (SDI)
unnamed: U180.2 (CKO), U181.5 (CKI)
unnamed: U180.3 (SDO), U181.4 (SDI)
unnamed: U181.2 (CKO), U182.5 (CKI)
unnamed: U181.3 (SDO), U182.4 (SDI)
unnamed: U182.2 (CKO), U183.5 (CKI)
unnamed: U182.3 (SDO), U183.4 (SDI)
unnamed: U183.2 (CKO), U184.5 (CKI)
unnamed: U183.3 (SDO), U184.4 (SDI)
unnamed: U184.2 (CKO), U185.5 (CKI)
unnamed: U184.3 (SDO), U185.4 (SDI)
unnamed: U185.2 (CKO), U186.5 (CKI)
unnamed: U185.3 (SDO), U186.4 (SDI)
unnamed: U186.2 (CKO), U187.5 (CKI)
unnamed: U186.3 (SDO), U187.4 (SDI)
unnamed: U187.2 (CKO), U188.5 (CKI)
unnamed: U187.3 (SDO), U188.4 (SDI)
unnamed: U188.2 (CKO), U189.5 (CKI)
unnamed: U188.3 (SDO), U189.4 (SDI)
unnamed: U189.2 (CKO), U190.5 (CKI)
unnamed: U189.3 (SDO), U190.4 (SDI)
unnamed: U190.2 (CKO), U191.5 (CKI)
unnamed: U190.3 (SDO), U191.4 (SDI)
unnamed: U191.2 (CKO), U192.5 (CKI)
unnamed: U191.3 (SDO), U192.4 (SDI)
unnamed: U193.2 (CKO), U194.5 (CKI)
unnamed: U193.3 (SDO), U194.4 (SDI)
unnamed: U194.2 (CKO), U195.5 (CKI)
unnamed: U194.3 (SDO), U195.4 (SDI)
unnamed: U195.2 (CKO), U196.5 (CKI)
unnamed: U195.3 (SDO), U196.4 (SDI)
unnamed: U196.2 (CKO), U197.5 (CKI)
unnamed: U196.3 (SDO), U197.4 (SDI)
unnamed: U197.2 (CKO), U198.5 (CKI)
unnamed: U197.3 (SDO), U198.4 (SDI)
unnamed: U198.2 (CKO), U199.5 (CKI)
unnamed: U198.3 (SDO), U199.4 (SDI)
unnamed: U199.2 (CKO), U200.5 (CKI)
unnamed: U199.3 (SDO), U200.4 (SDI)
unnamed: U200.2 (CKO), U201.5 (CKI)
unnamed: U200.3 (SDO), U201.4 (SDI)
unnamed: U201.2 (CKO), U202.5 (CKI)
unnamed: U201.3 (SDO), U202.4 (SDI)
unnamed: U202.2 (CKO), U203.5 (CKI)
unnamed: U202.3 (SDO), U203.4 (SDI)
unnamed: U203.2 (CKO), U204.5 (CKI)
unnamed: U203.3 (SDO), U204.4 (SDI)
unnamed: U204.2 (CKO), U205.5 (CKI)
unnamed: U204.3 (SDO), U205.4 (SDI)
unnamed: U205.2 (CKO), U206.5 (CKI)
unnamed: U205.3 (SDO), U206.4 (SDI)
unnamed: U206.2 (CKO), U207.5 (CKI)
unnamed: U206.3 (SDO), U207.4 (SDI)
unnamed: U207.2 (CKO), U208.5 (CKI)
unnamed: U207.3 (SDO), U208.4 (SDI)
unnamed: U209.2 (CKO), U210.5 (CKI)
unnamed: U209.3 (SDO), U210.4 (SDI)
unnamed: U210.2 (CKO), U211.5 (CKI)
unnamed: U210.3 (SDO), U211.4 (SDI)
unnamed: U211.2 (CKO), U212.5 (CKI)
unnamed: U211.3 (SDO), U212.4 (SDI)
unnamed: U212.2 (CKO), U213.5 (CKI)
unnamed: U212.3 (SDO), U213.4 (SDI)
unnamed: U213.2 (CKO), U214.5 (CKI)
unnamed: U213.3 (SDO), U214.4 (SDI)
unnamed: U214.2 (CKO), U215.5 (CKI)
unnamed: U214.3 (SDO), U215.4 (SDI)
unnamed: U215.2 (CKO), U216.5 (CKI)
unnamed: U215.3 (SDO), U216.4 (SDI)
unnamed: U216.2 (CKO), U217.5 (CKI)
unnamed: U216.3 (SDO), U217.4 (SDI)
unnamed: U217.2 (CKO), U218.5 (CKI)
unnamed: U217.3 (SDO), U218.4 (SDI)
unnamed: U218.2 (CKO), U219.5 (CKI)
unnamed: U218.3 (SDO), U219.4 (SDI)
unnamed: U219.2 (CKO), U220.5 (CKI)
unnamed: U219.3 (SDO), U220.4 (SDI)
unnamed: U220.2 (CKO), U221.5 (CKI)
unnamed: U220.3 (SDO), U221.4 (SDI)
unnamed: U221.2 (CKO), U222.5 (CKI)
unnamed: U221.3 (SDO), U222.4 (SDI)
unnamed: U222.2 (CKO), U223.5 (CKI)
unnamed: U222.3 (SDO), U223.4 (SDI)
unnamed: U223.2 (CKO), U224.5 (CKI)
unnamed: U223.3 (SDO), U224.4 (SDI)
unnamed: U225.2 (CKO), U226.5 (CKI)
unnamed: U225.3 (SDO), U226.4 (SDI)
unnamed: U226.2 (CKO), U227.5 (CKI)
unnamed: U226.3 (SDO), U227.4 (SDI)
unnamed: U227.2 (CKO), U228.5 (CKI)
unnamed: U227.3 (SDO), U228.4 (SDI)
unnamed: U228.2 (CKO), U229.5 (CKI)
unnamed: U228.3 (SDO), U229.4 (SDI)
unnamed: U229.2 (CKO), U230.5 (CKI)
unnamed: U229.3 (SDO), U230.4 (SDI)
unnamed: U230.2 (CKO), U231.5 (CKI)
unnamed: U230.3 (SDO), U231.4 (SDI)
unnamed: U231.2 (CKO), U232.5 (CKI)
unnamed: U231.3 (SDO), U232.4 (SDI)
unnamed: U232.2 (CKO), U233.5 (CKI)
unnamed: U232.3 (SDO), U233.4 (SDI)
unnamed: U233.2 (CKO), U234.5 (CKI)
unnamed: U233.3 (SDO), U234.4 (SDI)
unnamed: U234.2 (CKO), U235.5 (CKI)
unnamed: U234.3 (SDO), U235.4 (SDI)
unnamed: U235.2 (CKO), U236.5 (CKI)
unnamed: U235.3 (SDO), U236.4 (SDI)
unnamed: U236.2 (CKO), U237.5 (CKI)
unnamed: U236.3 (SDO), U237.4 (SDI)
unnamed: U237.2 (CKO), U238.5 (CKI)
unnamed: U237.3 (SDO), U238.4 (SDI)
unnamed: U238.2 (CKO), U239.5 (CKI)
unnamed: U238.3 (SDO), U239.4 (SDI)
unnamed: U239.2 (CKO), U240.5 (CKI)
unnamed: U239.3 (SDO), U240.4 (SDI)
unnamed: U241.2 (CKO), U242.5 (CKI)
unnamed: U241.3 (SDO), U242.4 (SDI)
unnamed: U242.2 (CKO), U243.5 (CKI)
unnamed: U242.3 (SDO), U243.4 (SDI)
unnamed: U243.2 (CKO), U244.5 (CKI)
unnamed: U243.3 (SDO), U244.4 (SDI)
unnamed: U244.2 (CKO), U245.5 (CKI)
unnamed: U244.3 (SDO), U245.4 (SDI)
unnamed: U245.2 (CKO), U246.5 (CKI)
unnamed: U245.3 (SDO), U246.4 (SDI)
unnamed: U246.2 (CKO), U247.5 (CKI)
unnamed: U246.3 (SDO), U247.4 (SDI)
unnamed: U247.2 (CKO), U248.5 (CKI)
unnamed: U247.3 (SDO), U248.4 (SDI)
unnamed: U248.2 (CKO), U249.5 (CKI)
unnamed: U248.3 (SDO), U249.4 (SDI)
unnamed: U249.2 (CKO), U250.5 (CKI)
unnamed: U249.3 (SDO), U250.4 (SDI)
unnamed: U250.2 (CKO), U251.5 (CKI)
unnamed: U250.3 (SDO), U251.4 (SDI)
unnamed: U251.2 (CKO), U252.5 (CKI)
unnamed: U251.3 (SDO), U252.4 (SDI)
unnamed: U252.2 (CKO), U253.5 (CKI)
unnamed: U252.3 (SDO), U253.4 (SDI)
unnamed: U253.2 (CKO), U254.5 (CKI)
unnamed: U253.3 (SDO), U254.4 (SDI)
unnamed: U254.2 (CKO), U255.5 (CKI)
unnamed: U254.3 (SDO), U255.4 (SDI)
unnamed: U255.2 (CKO), U256.5 (CKI)
unnamed: U255.3 (SDO), U256.4 (SDI)
SD1: U16.3 (SDO), U17.4 (SDI)
SD2: U32.3 (SDO), U33.4 (SDI)
SD3: U48.3 (SDO), U49.4 (SDI)
SD4: U64.3 (SDO), U65.4 (SDI)
SD5: U80.3 (SDO), U81.4 (SDI)
SD6: U96.3 (SDO), U97.4 (SDI)
SD7: U112.3 (SDO), U113.4 (SDI)
SD8: U128.3 (SDO), U129.4 (SDI)
SD9: U144.3 (SDO), U145.4 (SDI)
SD10: U160.3 (SDO), U161.4 (SDI)
SD11: U176.3 (SDO), U177.4 (SDI)
SD12: U192.3 (SDO), U193.4 (SDI)
SD13: U208.3 (SDO), U209.4 (SDI)
SD14: U224.3 (SDO), U225.4 (SDI)
SD15: U240.3 (SDO), U241.4 (SDI)
SDS: P1.3, U1.4 (SDI)
